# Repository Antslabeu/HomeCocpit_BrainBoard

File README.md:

# BrainBoard – STM32G0 CAN-FD Base Board

BrainBoard is a small base board built around an STM32G0B1KET6 MCU and a CAN-FD transceiver.
It is intended as a “brain” for various cockpit / IO modules, providing 3V3 power, CAN-FD
communication and a common expansion interface.

Repo: https://github.com/Antslabeu/HomeCocpit_BrainBoard  

> **Status:** prototype / WIP – use at your own risk.

---

## Main Features

- MCU: **STM32G0B1KET6**
  - CAN-FD, SPI, I²C, UART, timers/PWM, ADC, GPIO exposed on board connectors
- CAN-FD transceiver: **MCP2542FDxMF**
- Power architecture:
  - Input: **12 V**
  - On-board DC/DC step-down (2× **TPS62170DSG**):
    - **3.3 V / 1 A** rail for MCU and logic
    - **5 V** rail available on board
- PCB:
  - **4-layer** board, 1.6 mm
  - Stackup: **JLC04161H-7628** (JLCPCB)

---

## Programming Connector – `STM_PROG` (J1)

6-pin programming/debug connector for SWD + UART:

| Pin | Signal | Net    | Description                      |
|-----|--------|--------|----------------------------------|
| 1   | VCC    | 3.3V   | Target supply (3.3 V)           |
| 2   | DIO    | SW_DIO | SWD data I/O                    |
| 3   | RST    | SW_RST | MCU reset (NRST)                |
| 4   | CLK    | SW_CLK | SWD clock                       |
| 5   | TX     | SW_TX  | MCU UART TX (debug / bootloader)|
| 6   | GND    | GND    | Ground                          |

Compatible with ST-Link, J-Link and other SWD programmers.

---

## IO Connectors (Module Interface)

The board exposes module connectors that carry:

- **SPI bus** (shared)
- **4× chip select (CS) lines**
- **UART**
- **2× PWM outputs**
- **4× ADC inputs**
- **I²C bus** with **4.7 kΩ pull-ups** to 3.3 V
- **4× IO Board ID lines** – used to identify the type of module plugged into the connector  
  *(this Board ID mechanism is WIP and may change)*

Exact pinout is defined in the KiCad schematics (`connectors.kicad_sch`).

---

## CAN-FD Bus

- Transceiver: **MCP2542FDxMF** (CAN 2.0 / CAN FD up to 8 Mbit/s).
- CANH / CANL (and GND / power, if needed) are routed to dedicated connectors.
- Standard **120 Ω termination** is intended **only at the ends of the main bus**
  (check schematic for jumpers / solder bridges).

---

## Power

- **Input:** nominal **12 V**
- **Converters:** 2× **TPS62170DSG** buck regulators  
  (3 V–17 V in, up to 0.5 A each)  [Texas Instruments](https://www.ti.com/lit/ds/symlink/tps62170.pdf?utm_source=chatgpt.com)
- **Outputs:**
  - 12 V → **3.3 V / 1 A**
  - 12 V → **5 V** (aux rail)

### Typical consumption (board only, no external loads – rough estimate)

- STM32G0B1 in Run mode @ 64 MHz: typ. ~8–9 mA @ 3.3 V  [STMicroelectronics](https://www.st.com/resource/en/datasheet/stm32g0b1cc.pdf?utm_source=chatgpt.com)
- MCP2542FD supply current:
  - recessive: typ. ~2.5–5 mA @ 5 V
  - dominant: typ. ~55–70 mA @ 5 V  [DigiKey](https://www.digikey.kr/htmldatasheets/production/1897584/0/0/1/mcp2542-44fd-wfd.html?utm_source=chatgpt.com)
- TPS62170 quiescent current: ~17 µA from VIN each  [Texas Instruments](https://www.ti.com/lit/ds/symlink/tps62170.pdf?utm_source=chatgpt.com)

So, approximately:

- **Idle bus (recessive):**  
  - P_out ≈ 30 mW (MCU) + 25 mW (CAN) ≈ 55 mW  
  - With ~85% efficiency, input power ≈ 65 mW → **I_in ≈ 5–6 mA @ 12 V**
- **Worst-case dominant transmit:**  
  - P_out ≈ 30 mW (MCU) + 350 mW (CAN) ≈ 380 mW  
  - Input ≈ 450 mW → **I_in ≈ 35–40 mA @ 12 V**

Real current will be higher once external modules load 3.3 V rail.

Always respect absolute maximum ratings from datasheets.

---

## Files and Tools

All hardware files are in the repo root:

- `BrainBoard.kicad_pro` – main KiCad 8 project
- `BrainBoard.kicad_sch` + hierarchical sheets:
  - `power.kicad_sch`
  - `mcu.kicad_sch`
  - `can.kicad_sch`
  - `connectors.kicad_sch`
- `BrainBoard.kicad_pcb` – PCB layout (4-layer, JLC04161H-7628)
- `BrainBoard.pdf` – schematic PDF
- `LICENSE` – MIT

**CAD tool:** KiCad **8.x** (designed with 8.0.4).

---

## Getting Started (Hardware)

1. **Open the project**  
   Clone the repo and open `BrainBoard.kicad_pro` in KiCad 8.x.

2. **Review schematics and layout**  
   Check power, CAN and connector pinouts before manufacturing.

3. **Manufacturing**  
   - Generate Gerbers from KiCad.
   - Use the **JLC04161H-7628** 4-layer stackup if ordering from JLCPCB.

4. **First power-up**  
   - Apply **12 V** to the main power input.  
   - Verify 3.3 V and 5 V rails on test points.  
   - Connect a SWD programmer to **STM_PROG** and flash a simple test firmware
     (blink + CAN init).

5. **Integrate into CAN-FD network**  
   - Connect CANH/CANL to your main CAN-FD backbone.  
   - Enable 120 Ω termination only on physical bus ends.

---

## Firmware / Software

Firmware, examples and Board ID handling are **WIP** and not yet part of this repository.

Planned:

- Reference firmware for:
  - CAN-FD communication
  - SPI-based module control
  - Board ID-based module detection

---

## License

This hardware design is released under the **MIT License**  
(see the `LICENSE` file in the repository).

---

## Disclaimer

This is a prototype board.  
No guarantees are given – **use at your own risk**, especially in any safety-critical context.

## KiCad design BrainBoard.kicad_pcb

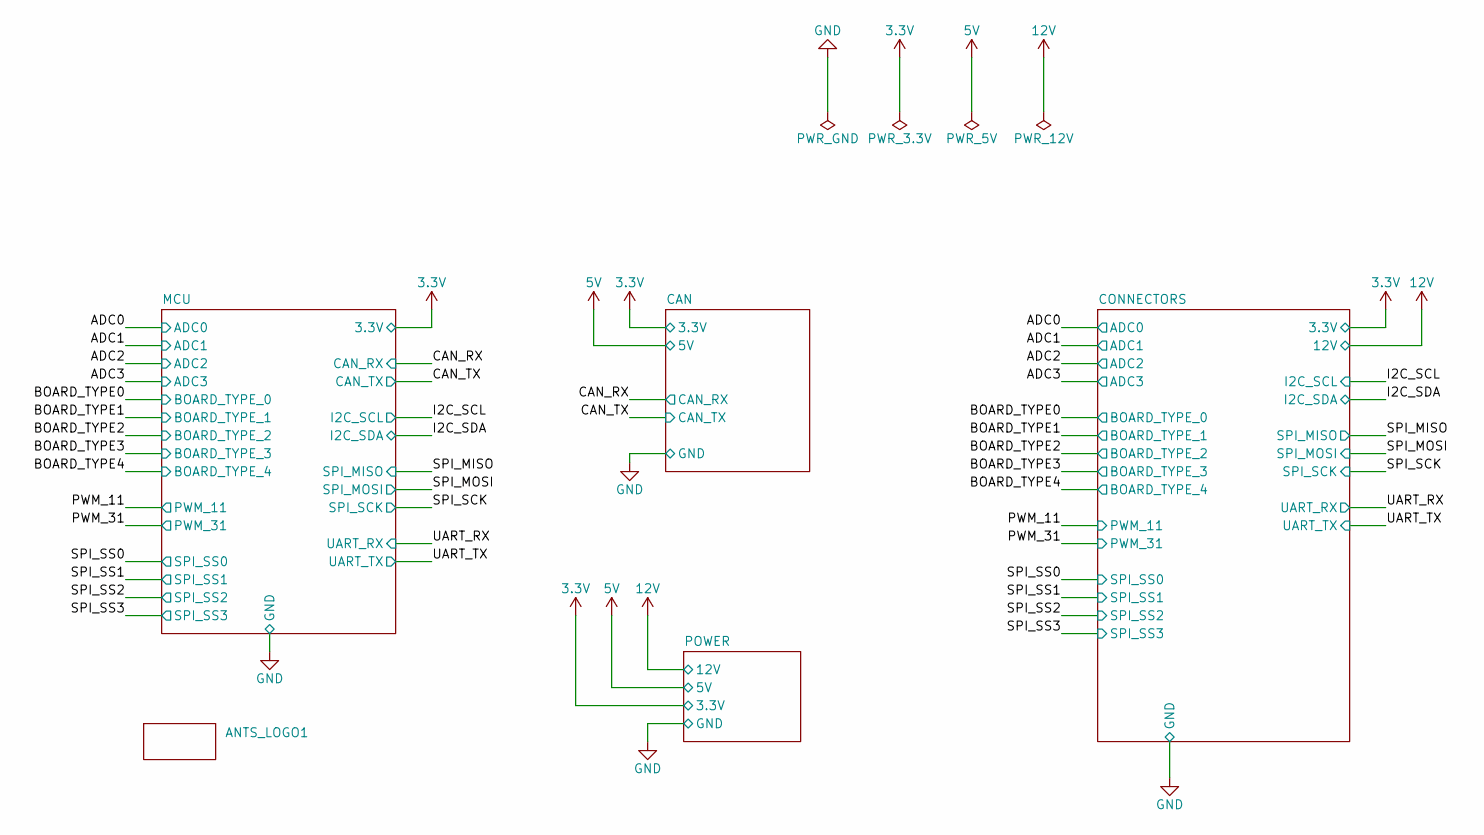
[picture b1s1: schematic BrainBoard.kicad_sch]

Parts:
ANTS_LOGO1: LOGO_H4

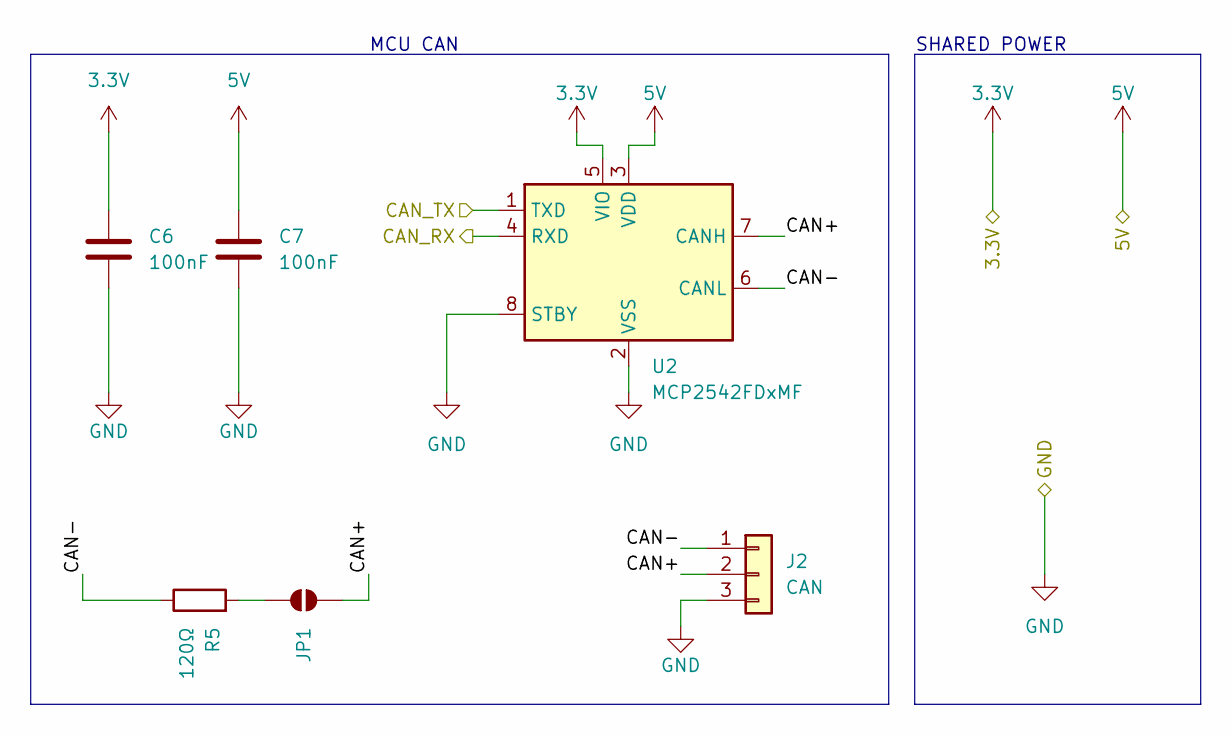
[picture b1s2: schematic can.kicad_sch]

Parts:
C6, C7: 100nF; C_0805_2012Metric
J2: CAN; JST_GH_BM03B-GHS-TBT_1x03-1MP_P1.25mm_Vertical
JP1: SolderJumper_2_Open; SolderJumper-2_P1.3mm_Open_RoundedPad1.0x1.5mm
R5: 120Ω; R_0805_2012Metric
U2: MCP2542FDxMF; SOIC-8_NO_PAD

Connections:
3.3V: C6.1, U2.5 (VIO); also elsewhere on the board
5V: C7.1, U2.3 (VDD); also elsewhere on the board
/CAN/CAN+: J2.2, JP1.2 (B), U2.7 (CANH)
/CAN/CAN-: J2.1, R5.1, U2.6 (CANL)
/CAN_RX: U2.4 (RXD); also elsewhere on the board
/CAN_TX: U2.1 (TXD); also elsewhere on the board
GND: C6.2, C7.2, J2.3, U2.2 (VSS), U2.8 (STBY); also elsewhere on the board
unnamed: JP1.1 (A), R5.2

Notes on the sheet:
SHARED POWER
MCU CAN

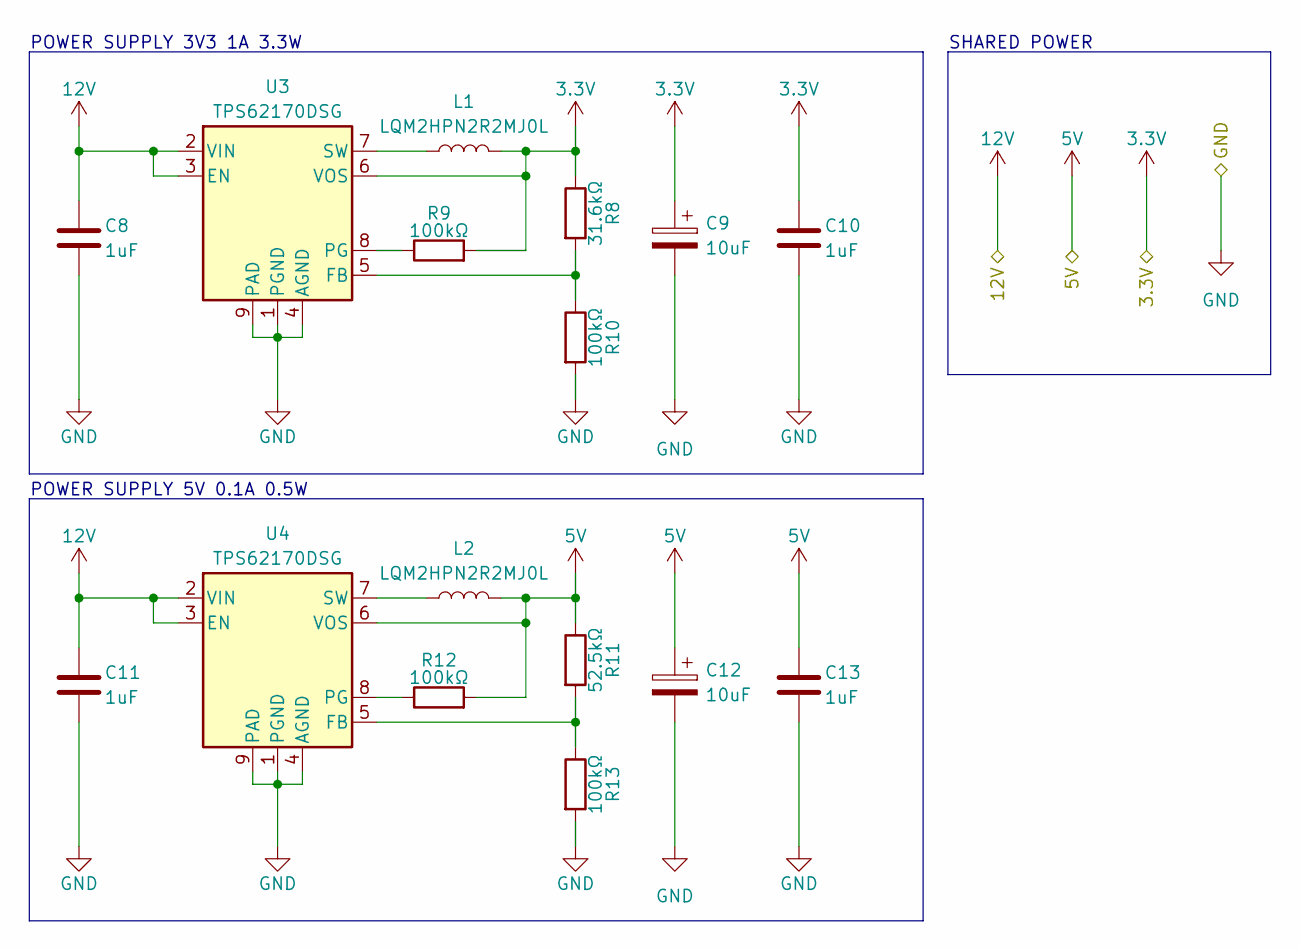
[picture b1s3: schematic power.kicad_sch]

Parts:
C8, C10, C11, C13: 1uF; C_0805_2012Metric
C9, C12: 10uF; CP_Elec_4x5.4
L1, L2: LQM2HPN2R2MJ0L; L_1008_2520Metric
R8: 31.6kΩ; R_0805_2012Metric
R9, R10, R12, R13: 100kΩ; R_0805_2012Metric
R11: 52.5kΩ; R_0805_2012Metric
U3, U4: TPS62170DSG; WSON-8-1EP_2x2mm_P0.5mm_EP0.9x1.6mm

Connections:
3.3V: C9.1, C10.1, L1.2, R8.1, R9.2, U3.6 (VOS); also elsewhere on the board
5V: C12.1, C13.1, L2.2, R11.1, R12.2, U4.6 (VOS); also elsewhere on the board
12V: C8.1, C11.1, U3.2 (VIN), U3.3 (EN), U4.2 (VIN), U4.3 (EN); also elsewhere on the board
GND: C8.2, C9.2, C10.2, C11.2, C12.2, C13.2, R10.2, R13.2, U3.1 (PGND), U3.4 (AGND), U3.9 (PAD), U4.1 (PGND), U4.4 (AGND), U4.9 (PAD); also elsewhere on the board
unnamed: R8.2, R10.1, U3.5 (FB)
unnamed: R9.1, U3.8 (PG)
unnamed: L1.1, U3.7 (SW)
unnamed: R11.2, R13.1, U4.5 (FB)
unnamed: R12.1, U4.8 (PG)
unnamed: L2.1, U4.7 (SW)

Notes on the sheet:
SHARED POWER
POWER SUPPLY 5V 0.1A 0.5W
POWER SUPPLY 3V3 1A 3.3W

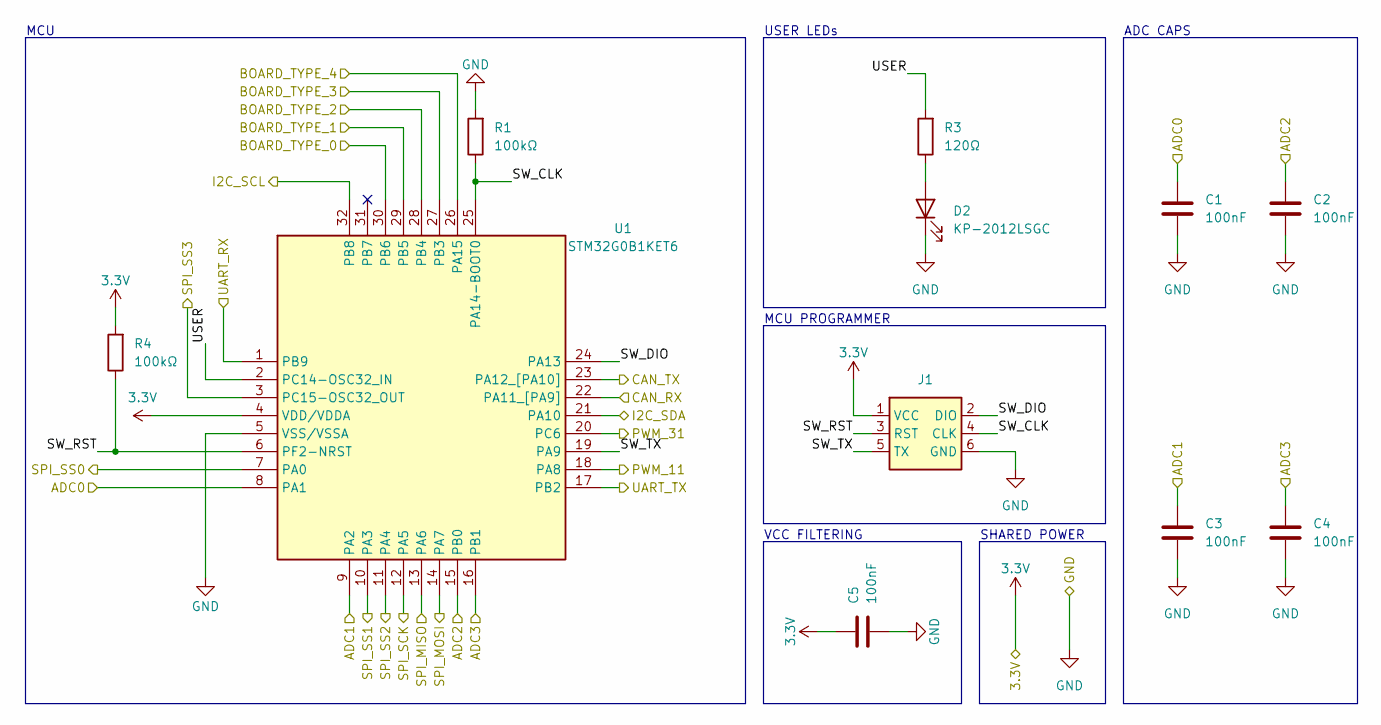
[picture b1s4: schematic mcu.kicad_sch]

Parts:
C1, C2, C3, C4, C5: 100nF; C_0805_2012Metric
D2: KP-2012LSGC; LED_0805_2012Metric
J1: PinSocket_2x03_P2.54mm_Vertical
R1, R4: 100kΩ; R_0805_2012Metric
R3: 120Ω; R_0805_2012Metric
U1: STM32G0B1KET6; LQFP-32_7x7mm_P0.8mm; Manufacturer_Part_Number STM32G0B1KET6

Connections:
3.3V: C5.1, J1.1 (VCC), R4.2, U1.4 (VDD/VDDA); also elsewhere on the board
/ADC0: C1.1, U1.8 (PA1); also elsewhere on the board
/ADC1: C3.1, U1.9 (PA2); also elsewhere on the board
/ADC2: C2.1, U1.15 (PB0); also elsewhere on the board
/ADC3: C4.1, U1.16 (PB1); also elsewhere on the board
/BOARD_TYPE0: U1.30 (PB6); also elsewhere on the board
/BOARD_TYPE1: U1.29 (PB5); also elsewhere on the board
/BOARD_TYPE2: U1.28 (PB4); also elsewhere on the board
/BOARD_TYPE3: U1.27 (PB3); also elsewhere on the board
/BOARD_TYPE4: U1.26 (PA15); also elsewhere on the board
/CAN_RX: U1.22 (PA11_[PA9]); also elsewhere on the board
/CAN_TX: U1.23 (PA12_[PA10]); also elsewhere on the board
/I2C_SCL: U1.32 (PB8); also elsewhere on the board
/I2C_SDA: U1.21 (PA10); also elsewhere on the board
/MCU/SW_CLK: J1.4 (CLK), R1.1, U1.25 (PA14-BOOT0)
/MCU/SW_DIO: J1.2 (DIO), U1.24 (PA13)
/MCU/SW_RST: J1.3 (RST), R4.1, U1.6 (PF2-NRST)
/MCU/SW_TX: J1.5 (TX), U1.19 (PA9)
/MCU/USER: R3.2, U1.2 (PC14-OSC32_IN)
/PWM_11: U1.18 (PA8); also elsewhere on the board
/PWM_31: U1.20 (PC6); also elsewhere on the board
/SPI_MISO: U1.13 (PA6); also elsewhere on the board
/SPI_MOSI: U1.14 (PA7); also elsewhere on the board
/SPI_SCK: U1.12 (PA5); also elsewhere on the board
/SPI_SS0: U1.7 (PA0); also elsewhere on the board
/SPI_SS1: U1.10 (PA3); also elsewhere on the board
/SPI_SS2: U1.11 (PA4); also elsewhere on the board
/SPI_SS3: U1.3 (PC15-OSC32_OUT); also elsewhere on the board
/UART_RX: U1.1 (PB9); also elsewhere on the board
/UART_TX: U1.17 (PB2); also elsewhere on the board
GND: C1.2, C2.2, C3.2, C4.2, C5.2, D2.1 (K), J1.6 (GND), R1.2, U1.5 (VSS/VSSA); also elsewhere on the board
unnamed: D2.2 (A), R3.1

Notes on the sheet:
SHARED POWER
VCC FILTERING
MCU
MCU PROGRAMMER
ADC CAPS
USER LEDs

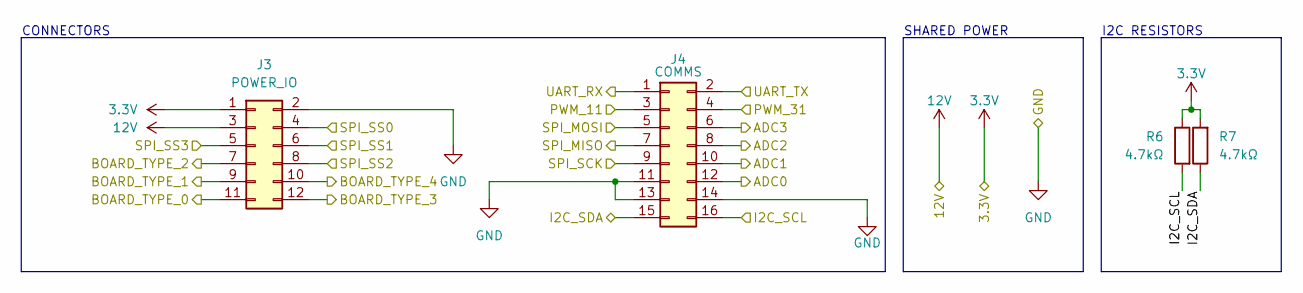
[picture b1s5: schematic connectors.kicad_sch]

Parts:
J3: POWER_IO; PinHeader_2x06_P2.54mm_Vertical
J4: COMMS; PinHeader_2x08_P2.54mm_Vertical
R6, R7: 4.7kΩ; R_0805_2012Metric

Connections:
3.3V: J3.1, R6.1, R7.2; also elsewhere on the board
12V: J3.3; also elsewhere on the board
/ADC0: J4.12; also elsewhere on the board
/ADC1: J4.10; also elsewhere on the board
/ADC2: J4.8; also elsewhere on the board
/ADC3: J4.6; also elsewhere on the board
/BOARD_TYPE0: J3.11; also elsewhere on the board
/BOARD_TYPE1: J3.9; also elsewhere on the board
/BOARD_TYPE2: J3.7; also elsewhere on the board
/BOARD_TYPE3: J3.12; also elsewhere on the board
/BOARD_TYPE4: J3.10; also elsewhere on the board
/I2C_SCL: J4.16, R6.2; also elsewhere on the board
/I2C_SDA: J4.15, R7.1; also elsewhere on the board
/PWM_11: J4.3; also elsewhere on the board
/PWM_31: J4.4; also elsewhere on the board
/SPI_MISO: J4.7; also elsewhere on the board
/SPI_MOSI: J4.5; also elsewhere on the board
/SPI_SCK: J4.9; also elsewhere on the board
/SPI_SS0: J3.4; also elsewhere on the board
/SPI_SS1: J3.6; also elsewhere on the board
/SPI_SS2: J3.8; also elsewhere on the board
/SPI_SS3: J3.5; also elsewhere on the board
/UART_RX: J4.1; also elsewhere on the board
/UART_TX: J4.2; also elsewhere on the board
GND: J3.2, J4.11, J4.13, J4.14; also elsewhere on the board

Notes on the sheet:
SHARED POWER
I2C RESISTORS
CONNECTORS

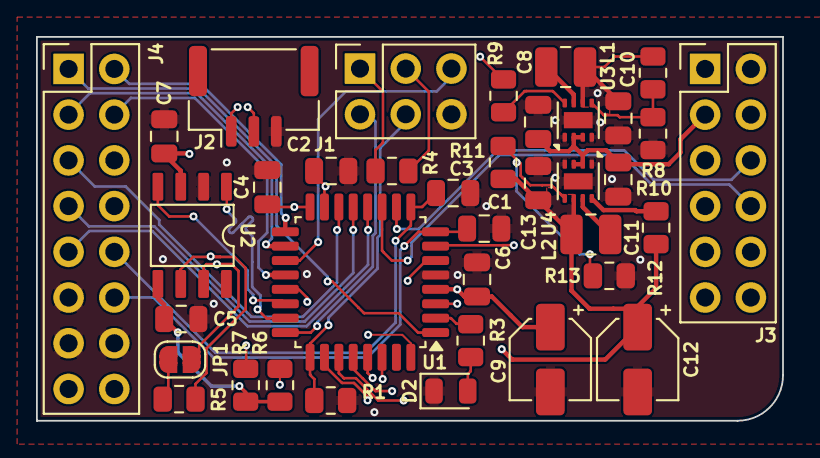
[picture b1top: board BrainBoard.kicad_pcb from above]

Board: 4 copper layers, 41.4 x 21.3 mm, 38 parts (1 on the bottom side), 43 nets.

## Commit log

2025-12-07 Initial commit
    Initial commit - added functions
2025-12-07 Changed CAN port to 3pin;
2025-12-11 Schematic overhaul: Added separated sheets for functions, Added 5V DCDC, Board overhaul: Modified to be MFR ready, Added 5V DCDC,
2025-12-11 Updated gitignore for manufacturing outputs
2025-12-11 Add README
    Added detailed documentation for the BrainBoard, including features, connectors, power specifications, and getting started instructions.
